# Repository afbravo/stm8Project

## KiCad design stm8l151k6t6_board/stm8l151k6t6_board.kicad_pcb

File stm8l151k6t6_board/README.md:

# STM8L151 Dev Board

This board was created with the intent to familiarize with the STM8 family of MCUs from ST Microcontroller.
The main features of this board are:

- micro usb power input
- power on led
- user led connected to PB0
- user button connected to PD7
- SWIM programming / debugging interface
- 8MHz High Speed External Clock
- 32.768 KHz Low Speed External Clock
- Reset Button
- General Male Headers for all I/O

The board was created using KiCad 6. It was mostly left up to the end user to decide its purspose
as it doesnt provide any internal sensors or ICs.

The DataSheet for the STM8L151K6T6 MCU: [datasheet](https://www.st.com/content/ccc/resource/technical/document/datasheet/43/12/db/4c/8b/08/4a/73/CD00240181.pdf/files/CD00240181.pdf/jcr:content/translations/en.CD00240181.pdf)

## Schematic

## PCB

## Finished Board

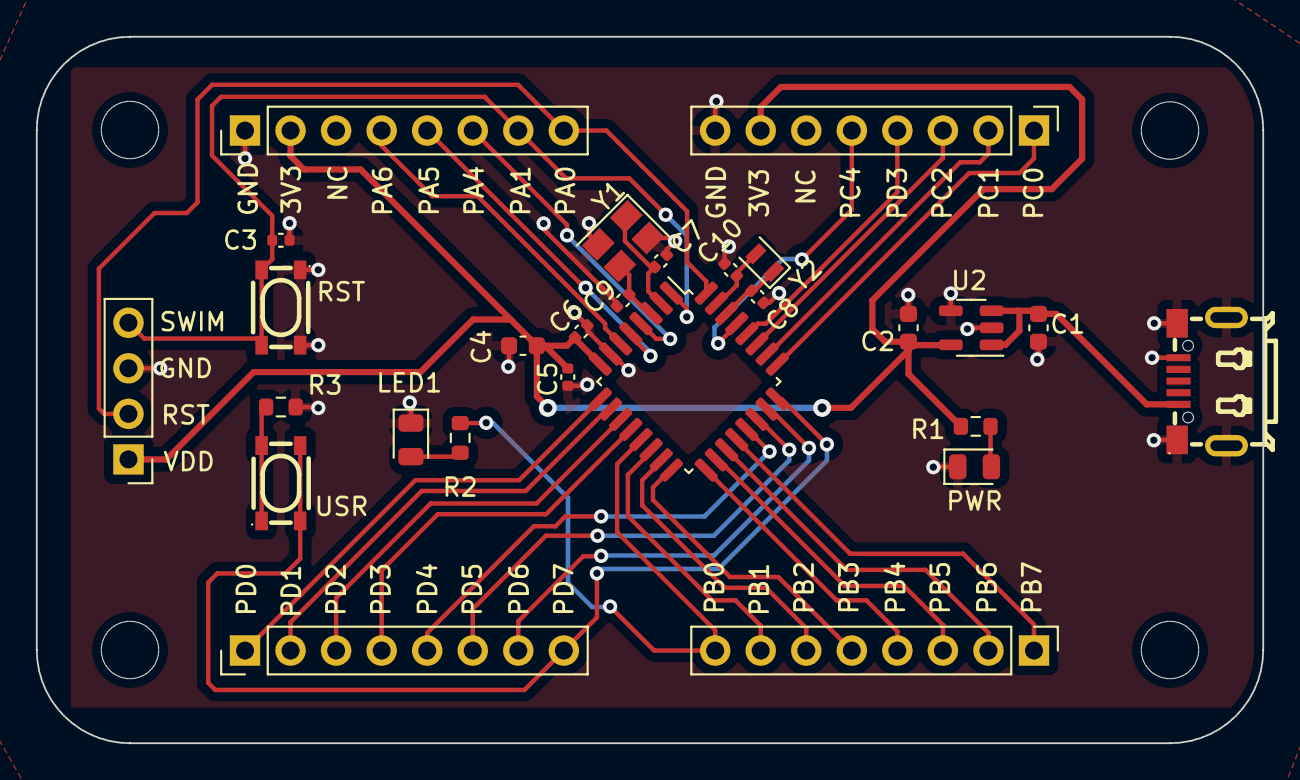
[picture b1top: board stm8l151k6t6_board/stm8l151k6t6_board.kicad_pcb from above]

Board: 2 copper layers, 68.4 x 39.4 mm, 31 parts (0 on the bottom side), 36 nets.

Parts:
C1, C2, C4: 1uF; C_0603_1608Metric
C3, C5, C6: 100nF; C_0402_1005Metric
C7, C8, C9, C10: 15pF; C_0402_1005Metric
H1, H2, H3, H4: MountingHole; MountingHole_3.2mm_M3
J1, J2, J3, J4: Conn_01x08; PinHeader_1x08_P2.54mm_Vertical
J5: Conn_01x04; PinHeader_1x04_P2.54mm_Vertical
LED1: RED; LED_0805_2012Metric
PWR: GREEN; LED_0805_2012Metric
R1, R2, R3: 100; R_0603_1608Metric
RST: RESET; SW-SMD_4P-L4.2-W3.2-P2.20-LS4.6
U1: USB_B_Micro; MICRO-USB-SMD_MICRO-7.2JB
U2: TPMIC5504; SOT-23-5
U3: STM8L151K6T6; LQFP-32_7x7mm_P0.8mm
USR: USER; SW-SMD_4P-L4.2-W3.2-P2.20-LS4.6
Y1: 8MHz; Crystal_SMD_3225-4Pin_3.2x2.5mm
Y2: 32K768Hz; Crystal_SMD_2012-2Pin_2.0x1.2mm

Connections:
+3V3: C2.1, C4.1, C5.1, C6.1, J1.2, J3.7, J5.1, R1.1, U2.5 (OUT), U3.8 (V_{DD})
+5V: C1.1, U1.1 (VBUS), U2.1 (IN), U2.3 (EN)
/HSE_IN: C7.1, U3.2 (PA2), Y1.1
/HSE_OUT: C9.1, U3.3 (PA3), Y1.3
/LSE_IN: C8.1, U3.30 (PC5), Y2.1
/LSE_OUT: C10.1, U3.31 (PC6), Y2.2
/PA0: J1.8, J5.2, U3.32 (PA0)
/PA1: C3.1, J1.7, J5.4, RST.3, RST.4, U3.1 (PA1/NRST)
/PA4: J1.6, U3.4 (PA4)
/PA5: J1.5, U3.5 (PA5)
/PA6: J1.4, U3.6 (PA6)
/PB0: J2.8, R2.1, U3.13 (PB0)
/PB1: J2.7, U3.14 (PB1)
/PB2: J2.6, U3.15 (PB2)
/PB3: J2.5, U3.16 (PB3)
/PB4: J2.4, U3.17 (PB4)
/PB5: J2.3, U3.18 (PB5)
/PB6: J2.2, U3.19 (PB6)
/PB7: J2.1, U3.20 (PB7)
/PC0: J3.1, U3.25 (PC0)
/PC1: J3.2, U3.26 (PC1)
/PC2: J3.3, U3.27 (PC2)
/PC3: J3.4, U3.28 (PC3)
/PC4: J3.5, U3.29 (PC4)
/PD0: J4.1, U3.9 (PD0)
/PD1: J4.2, U3.10 (PD1)
/PD2: J4.3, U3.11 (PD2)
/PD3: J4.4, U3.12 (PD3)
/PD4: J4.5, U3.21 (PD4)
/PD5: J4.6, U3.22 (PD5)
/PD6: J4.7, U3.23 (PD6)
/PD7: J4.8, U3.24 (PD7), USR.3, USR.4
GND: C1.2, C2.2, C3.2, C4.2, C5.2, C6.2, C7.2, C8.2, C9.2, C10.2, J1.1, J3.8, J5.3, LED1.1 (K), PWR.1 (K), R3.2, RST.1, RST.2, U1.5 (GND), U1.6 (EP), U1.7 (EP), U1.8 (EP), U1.9 (EP), U2.2 (GND), U2.4 (GND), U3.7 (V_{SS}), Y1.2, Y1.4
unnamed: PWR.2 (A), R1.2
unnamed: LED1.2 (A), R2.2
unnamed: R3.1, USR.1, USR.2

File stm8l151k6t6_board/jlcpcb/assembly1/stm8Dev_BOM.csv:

"Item","Qty","Reference(s)","Value","LibPart","Footprint","Datasheet","LCSC"
"1","3","C1, C2, C4","1uF","Device:C_Small","Capacitor_SMD:C_0603_1608Metric","~","C108463"
"2","3","C3, C5, C6","100nF","Device:C_Small","Capacitor_SMD:C_0402_1005Metric","~","C106252"
"3","4","C7, C8, C9, C10","15pF","Device:C_Small","Capacitor_SMD:C_0402_1005Metric","~","C295959"
"4","1","D1","GREEN","Device:LED","LED_SMD:LED_0805_2012Metric","~","C84257"
"5","1","D2","RED","Device:LED","LED_SMD:LED_0805_2012Metric","~","C113551"
"6","4","H1, H2, H3, H4","MountingHole","Mechanical:MountingHole","MountingHole:MountingHole_3.2mm_M3","~",""
"7","4","J1, J2, J3, J4","Conn_01x08","Connector_Generic:Conn_01x08","Connector_PinHeader_2.54mm:PinHeader_1x08_P2.54mm_Vertical","~",""
"8","1","J5","Conn_01x04","Connector_Generic:Conn_01x04","Connector_PinHeader_2.54mm:PinHeader_1x04_P2.54mm_Vertical","~",""
"9","3","R1, R2, R3","100","Device:R","Resistor_SMD:R_0603_1608Metric","~","C5139650"
"10","1","SW1","RESET","Switch:SKRPABE010","Button_Switch_SMD:SW-SMD_4P-L4.2-W3.2-P2.20-LS4.6","https://item.szlcsc.com/157210.html","C115360"
"11","1","SW2","USER","Switch:SKRPABE010","Button_Switch_SMD:SW-SMD_4P-L4.2-W3.2-P2.20-LS4.6","https://item.szlcsc.com/157210.html","C115360"
"12","1","U1","USB_B_Micro","Connector:MICRO_7_2JB","Connector_USB:MICRO-USB-SMD_MICRO-7.2JB","https://item.szlcsc.com/2777179.html","C2681559"
"13","1","U2","TPMIC5504","Regulator_Linear:TPMIC5504","Package_TO_SOT_SMD:SOT-23-5","http://www.ti.com/lit/gpn/tps782","C3021093"
"14","1","U3","STM8L151K6T6","MCU_ST_STM8:STM8L151K6T6","Package_QFP:LQFP-32_7x7mm_P0.8mm","https://www.mouser.com/datasheet/2/389/stm8l151c4-1851438.pdf","C8259"
"15","1","Y1","8MHz","Device:Crystal_GND24","Crystal:Crystal_SMD_3225-4Pin_3.2x2.5mm","~","C524715"
"16","1","Y2","32K768Hz","Device:Crystal","Crystal:Crystal_SMD_2012-2Pin_2.0x1.2mm","~","C90943"

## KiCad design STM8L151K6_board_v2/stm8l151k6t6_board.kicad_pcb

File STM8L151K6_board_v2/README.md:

# STM8L151 Dev Board V2.0

This board was created with the intent to familiarize with the STM8 family of MCUs from ST Microcontroller.
The main features of this board are:

- Micro usb power input
- Power on led
- User led connected to PB0
- User button connected to PD7
- SWIM programming / debugging interface
- 8MHz High Speed External Clock
- 32.768 KHz Low Speed External Clock
- Reset Button
- Generick Male Headers for all I/O
- USB to UART converter
- Breadboard friendly
- 2 layer PCB for inexpensive manufacturing

## Version 2.0 Improvements

The following features were added/removed from the previous version:

- Increase resistor value for internal leds to reduce brightness.
- Added USB to UART converter.
- Reduced form factor to 18mm wide by 48mm long, in order to fit in a breadboard.
- Changed the male headers to use 2 1x16 headers instead of 4 1x8 headers.
- Male headers are spaced to fit in a breadboard.
- Kept backwards compatibility with the previous version on connection of internal peripherals.
- Mechanical mounting holes were changed to m2 2.2mm diameter holes.

The board was created using KiCad 6. It was mostly left up to the end user to decide its purspose
as it doesnt provide any internal sensors or ICs.

The DataSheet for the STM8L151K6T6 MCU: [datasheet](https://www.st.com/content/ccc/resource/technical/document/datasheet/43/12/db/4c/8b/08/4a/73/CD00240181.pdf/files/CD00240181.pdf/jcr:content/translations/en.CD00240181.pdf)

## Schematic

## PCB

## Finished Board

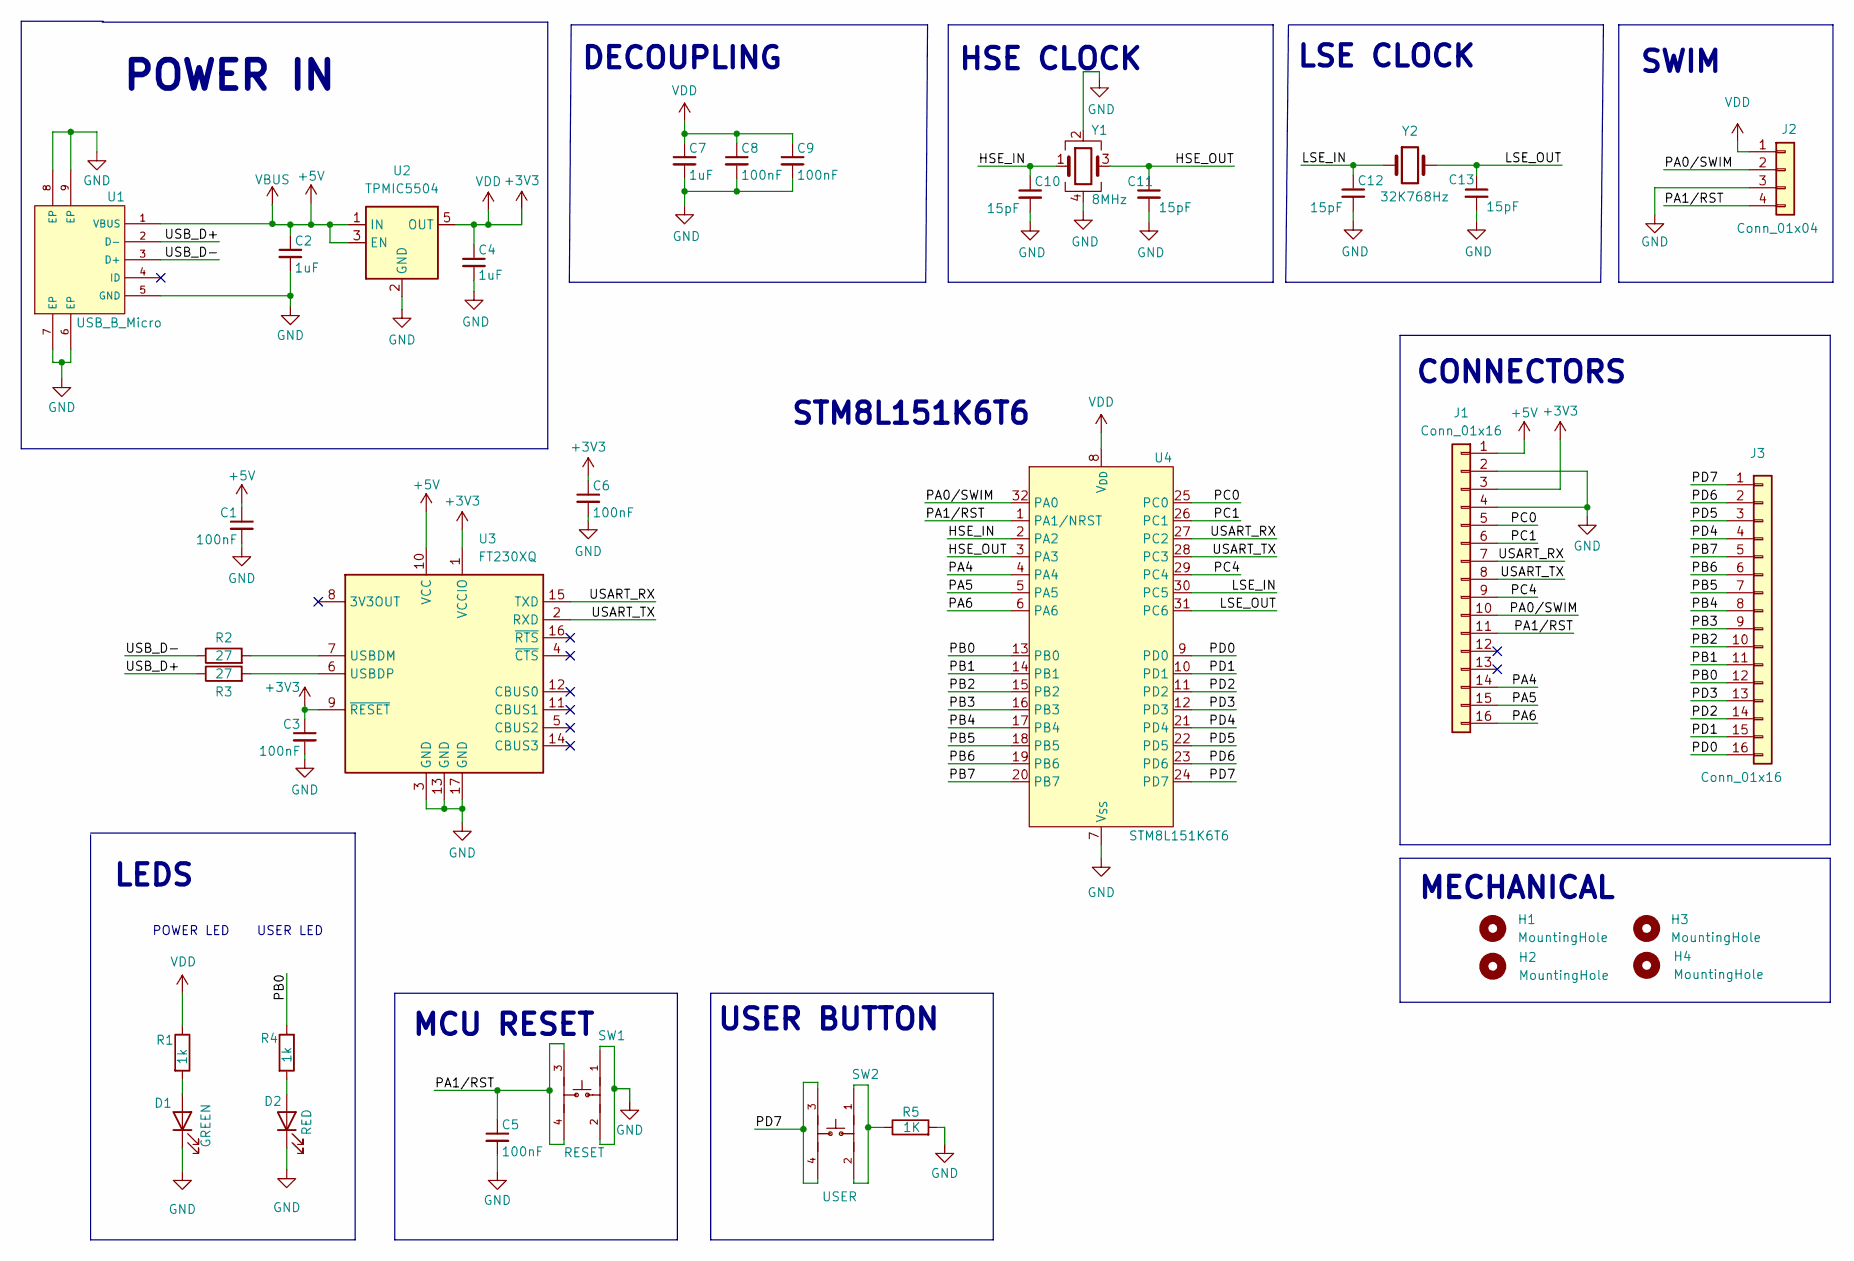
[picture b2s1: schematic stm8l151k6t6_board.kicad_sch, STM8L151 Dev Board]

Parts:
C1, C3, C5, C6, C8, C9: 100nF; C_0402_1005Metric; LCSC C106252
C2, C4, C7: 1uF; C_0603_1608Metric; LCSC C108463
C10, C11, C12, C13: 15pF; C_0402_1005Metric; LCSC C295959
D1: GREEN; LED_0805_2012Metric; LCSC C84257
D2: RED; LED_0805_2012Metric; LCSC C113551
H1, H2, H3, H4: MountingHole; MountingHole_2.2mm_M2
J1, J3: Conn_01x16; PinHeader_1x16_P2.54mm_Vertical
J2: Conn_01x04; PinHeader_1x04_P2.54mm_Vertical
R1, R4: 1k; R_0603_1608Metric
R2, R3: 27; R_0805_2012Metric; LCSC C352233
R5: 1K; R_0603_1608Metric; LCSC C5139650
SW1: RESET; SW-SMD_4P-L4.2-W3.2-P2.20-LS4.6; LCSC C115360
SW2: USER; SW-SMD_4P-L4.2-W3.2-P2.20-LS4.6; LCSC C115360
U1: USB_B_Micro; MICRO-USB-SMD_MICRO-7.2JB; LCSC C2681559
U2: TPMIC5504; SOT-23-5; LCSC C3021093
U3: FT230XQ; QFN-16-1EP_4x4mm_P0.65mm_EP2.1x2.1mm; LCSC C128629
U4: STM8L151K6T6; LQFP-32_7x7mm_P0.8mm; LCSC C8259
Y1: 8MHz; Crystal_SMD_3225-4Pin_3.2x2.5mm; LCSC C524715
Y2: 32K768Hz; Crystal_SMD_2012-2Pin_2.0x1.2mm; LCSC C90943

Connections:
+3V3: C3.1, C4.1, C6.1, C7.1, C8.1, C9.1, J1.3, J2.1, R1.1, U2.5 (OUT), U3.1 (VCCIO), U3.9 (~RESET), U4.8 (V_{DD})
+5V: C1.1, C2.1, J1.1, U1.1 (VBUS), U2.1 (IN), U2.3 (EN), U3.10 (VCC)
/HSE_IN: C10.1, U4.2 (PA2), Y1.1
/HSE_OUT: C11.1, U4.3 (PA3), Y1.3
/LSE_IN: C12.1, U4.30 (PC5), Y2.1
/LSE_OUT: C13.1, U4.31 (PC6), Y2.2
/PA0/SWIM: J1.10, J2.2, U4.32 (PA0)
/PA1/RST: C5.1, J1.11, J2.4, SW1.3, SW1.4, U4.1 (PA1/NRST)
/PA4: J1.14, U4.4 (PA4)
/PA5: J1.15, U4.5 (PA5)
/PA6: J1.16, U4.6 (PA6)
/PB0: J3.12, R4.1, U4.13 (PB0)
/PB1: J3.11, U4.14 (PB1)
/PB2: J3.10, U4.15 (PB2)
/PB3: J3.9, U4.16 (PB3)
/PB4: J3.8, U4.17 (PB4)
/PB5: J3.7, U4.18 (PB5)
/PB6: J3.6, U4.19 (PB6)
/PB7: J3.5, U4.20 (PB7)
/PC0: J1.5, U4.25 (PC0)
/PC1: J1.6, U4.26 (PC1)
/PC4: J1.9, U4.29 (PC4)
/PD0: J3.16, U4.9 (PD0)
/PD1: J3.15, U4.10 (PD1)
/PD2: J3.14, U4.11 (PD2)
/PD3: J3.13, U4.12 (PD3)
/PD4: J3.4, U4.21 (PD4)
/PD5: J3.3, U4.22 (PD5)
/PD6: J3.2, U4.23 (PD6)
/PD7: J3.1, SW2.3, SW2.4, U4.24 (PD7)
/USART_RX: J1.7, U3.15 (TXD), U4.27 (PC2)
/USART_TX: J1.8, U3.2 (RXD), U4.28 (PC3)
/USB_D+: R3.1, U1.2 (D-)
/USB_D-: R2.1, U1.3 (D+)
GND: C1.2, C2.2, C3.2, C4.2, C5.2, C6.2, C7.2, C8.2, C9.2, C10.2, C11.2, C12.2, C13.2, D1.1 (K), D2.1 (K), J1.2, J1.4, J2.3, R5.2, SW1.1, SW1.2, U1.5 (GND), U1.6 (EP), U1.7 (EP), U1.8 (EP), U1.9 (EP), U2.2 (GND), U2.4 (GND), U3.3 (GND), U3.13 (GND), U3.17 (GND), U4.7 (V_{SS}), Y1.2, Y1.4
unnamed: D1.2 (A), R1.2
unnamed: D2.2 (A), R4.2
unnamed: R5.1, SW2.1, SW2.2
unnamed: R2.2, U3.7 (USBDM)
unnamed: R3.2, U3.6 (USBDP)

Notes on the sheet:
POWER LED
LSE CLOCK
STM8L151K6T6
SWIM
HSE CLOCK
CONNECTORS
MCU RESET
USER BUTTON
POWER IN
USER LED
LEDS
DECOUPLING
MECHANICAL

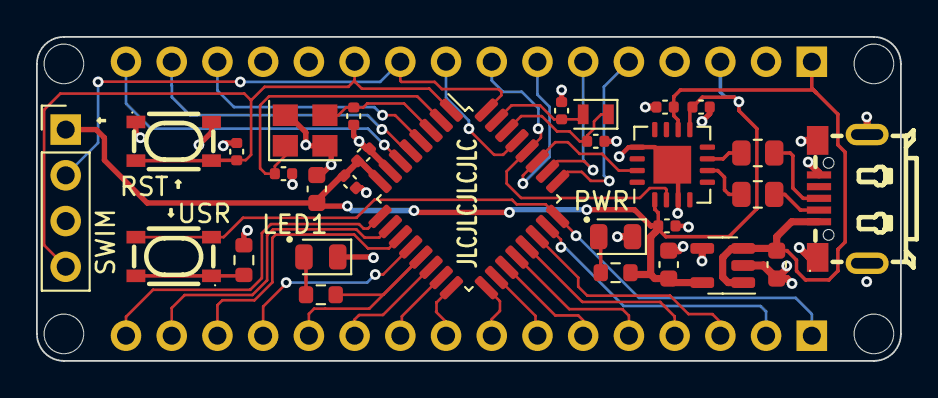
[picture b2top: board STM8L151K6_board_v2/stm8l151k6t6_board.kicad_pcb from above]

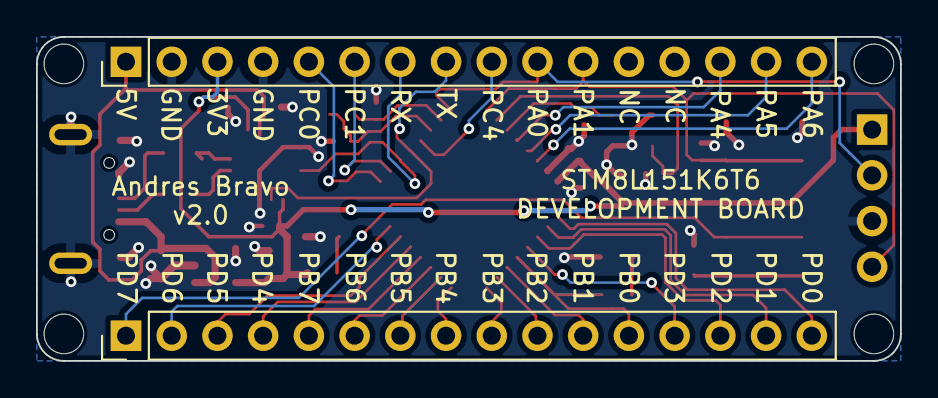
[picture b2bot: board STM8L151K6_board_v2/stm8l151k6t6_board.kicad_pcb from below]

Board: 2 copper layers, 48.0 x 18.0 mm, 35 parts (2 on the bottom side), 40 nets.
